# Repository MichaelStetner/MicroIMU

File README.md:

# MicroIMU
Gryo, accelerometer, and compass on a very small PCB

This project is inspired by [Pololu's MinIMU](https://www.pololu.com/product/2738). We redesigned  The design was changed for our particular application: simultaneous recording of neural activity and body movements. To record body movements, the MicroIMU is attached to an animal. To minimize the animal's discomfort, the MicroIMU needs to be as small and light as possible.
Alongside the MicroIMU, neural activity is recorded with sensitive analog electronics (not included in this repository). To protect the analog electronics, they must be shielded from intereference coming from the digital signals on the MicroIMU so the PCB contains power and ground planes.

Compared to MinIMU, MicroIMU has the following improvements:
* Smaller board size
* Reduced weight
* Power and ground planes
* Wider input voltage range: 2.5V-30V, up from 2.5V-5.5V

Here are the ways that this MicroIMU is less desirable than Pololu's MinIMU:
* 4 PCB layers, up from 2 (increases manufacturing cost)
* 3.3V I2C communication, down from 5V (compatible with Arduino Due, but not Arduino Uno)
* Less stable power supply (fewer bypass capacitors)
* No external connections for VDD (3.3V) or SA0 (least significant bit of I2C address)

### Acknowledgements
* EAGLE libraries from openrobots-dev/Eagle

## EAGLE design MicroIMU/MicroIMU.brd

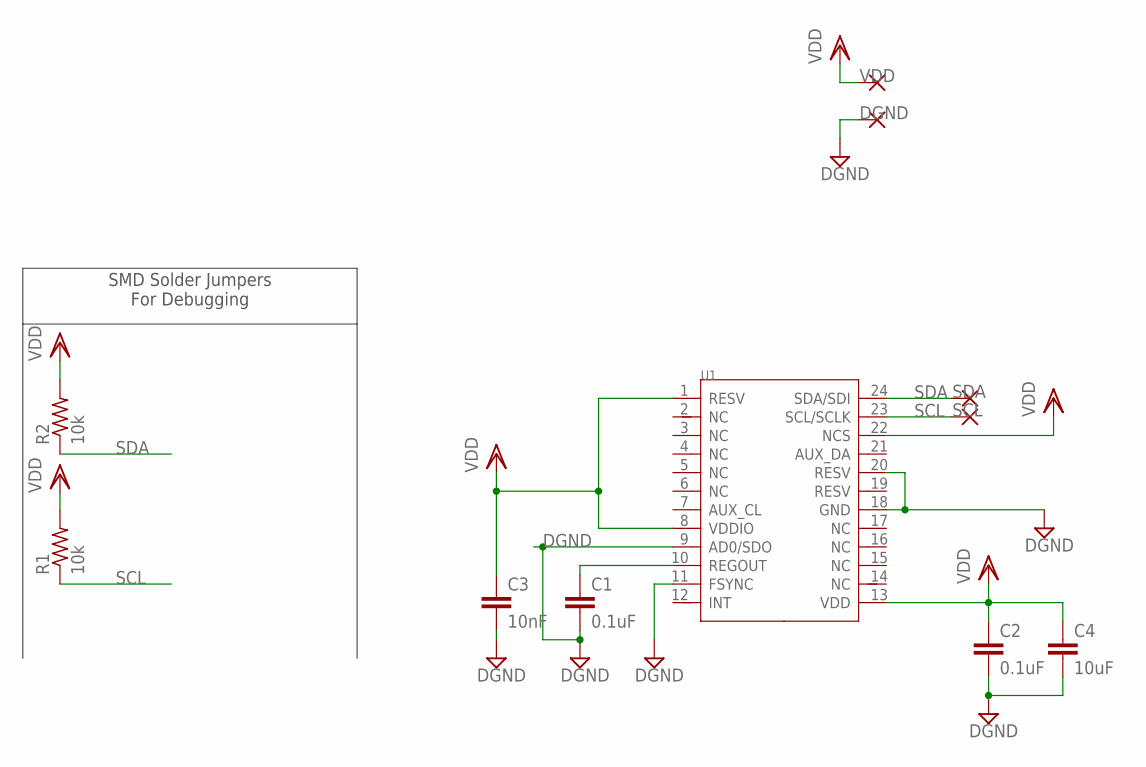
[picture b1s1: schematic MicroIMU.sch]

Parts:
C1, C2: 0.1uF; C0402
C3: 10nF; C0402
C4: 10uF; C0603
DGND: THROUGH-HOLE-30MIL/15MIL; 30MIL/15MIL
R1, R2: 10k; R0201
SCL: THROUGH-HOLE-30MIL/15MIL; 30MIL/15MIL
SDA: THROUGH-HOLE-30MIL/15MIL; 30MIL/15MIL
U1: MPU-9250; LEAD-QFN24
VDD: THROUGH-HOLE-30MIL/15MIL; 30MIL/15MIL

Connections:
DGND: C1.2, C2.2, C3.2, C4.2, DGND.P$1, U1.9 (AD0/SDO), U1.11 (FSYNC), U1.18 (GND), U1.20 (RESV)
unnamed: C1.1, U1.10 (REGOUT)
SCL: R1.1, SCL.P$1, U1.23 (SCL/SCLK)
SDA: R2.1, SDA.P$1, U1.24 (SDA/SDI)
VDD: C2.1, C3.1, C4.1, R1.2, R2.2, U1.1 (RESV), U1.8 (VDDIO), U1.13 (VDD), U1.22 (NCS), VDD.P$1

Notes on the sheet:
SMD Solder Jumpers For Debugging

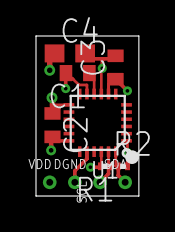
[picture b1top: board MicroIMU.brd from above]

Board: 4 copper layers, 5.7 x 8.9 mm, 11 parts (0 on the bottom side), 5 nets.

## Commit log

2015-11-16 README now contains description of the project
2015-11-16 st.lbr added, copied from openrobots-dev/Eagle
2015-11-16 Added board and schematic - halfway done with routing
2015-11-16 Done routing
2015-11-16 Galen made minor layout changes to save space
2015-11-16 Added labels to silkscreen layer
2015-11-16 Improved silkscreen labels
2015-11-16 Galen rearranged the board again - rotated the LSM303DLHC by 90 degrees
2015-11-16 More rearrangement by Galen - everything is much closer together now
2015-11-16 Galen switched to LSM303D for accelerometer/compass - newer design with smaller package
2015-11-16 Added missing connections for CS and SA0 on LSM303D
2015-11-17 Rotated L3GD20H so that X and Y axes of the two chips are aligned
2015-11-17 Silkscreen updated
2017-02-11 changed to invense MPU9250
2017-03-12 cleaned up files
